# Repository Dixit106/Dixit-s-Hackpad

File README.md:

# Dixit's Hackpad

This is a custom 6-key macropad with a rotary encoder designed for the Hack Club Onboard program.

## Features

* 6 Mechanical Switches (Cherry MX style)
* 1 Rotary Encoder (for volume/scrolling)
* 2 RGB LEDs (SK6812 MINI-E)
* Powered by Seeed XIAO RP2040
* Custom 3D Printed Case (PLA) with snap-fit lid
* Custom PCB Art

## Bill of Materials (BOM)

| Part            | Quantity | Description                               |
| :-------------- | :------- | :---------------------------------------- |
| Microcontroller | 1        | Seeed Studio XIAO RP2040                  |
| Switches        | 6        | Cherry MX Compatible Mechanical Switches  |
| Rotary Encoder  | 1        | EC11 Rotary Encoder                       |
| LEDs            | 2        | SK6812 MINI-E RGB LEDs                    |
| Case            | 1        | Custom 3D Printed PLA Case (Top & Bottom) |
| PCB             | 1        | Custom Designed PCB                       |

## Gallery

### PCB Design

### Schematic

### 3D Case Design

Final:-(i messed up 3d printed case while i was trying to customize it irl)

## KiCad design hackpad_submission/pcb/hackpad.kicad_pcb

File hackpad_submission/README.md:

# Dixit's Hackpad

This is a custom 6-key macropad with a rotary encoder designed for the Hack Club Onboard program.

## Features

* 6 Mechanical Switches (Cherry MX style)
* 1 Rotary Encoder (for volume/scrolling)
* 2 RGB LEDs (SK6812 MINI-E)
* Powered by Seeed XIAO RP2040
* Custom 3D Printed Case (PLA) with snap-fit lid
* Custom PCB Art

## Bill of Materials (BOM)

| Part            | Quantity | Description                               |
| :-------------- | :------- | :---------------------------------------- |
| Microcontroller | 1        | Seeed Studio XIAO RP2040                  |
| Switches        | 6        | Cherry MX Compatible Mechanical Switches  |
| Rotary Encoder  | 1        | EC11 Rotary Encoder                       |
| LEDs            | 2        | SK6812 MINI-E RGB LEDs                    |
| Case            | 1        | Custom 3D Printed PLA Case (Top & Bottom) |
| PCB             | 1        | Custom Designed PCB                       |

## Gallery

### PCB Design

### Schematic

### 3D Case Design

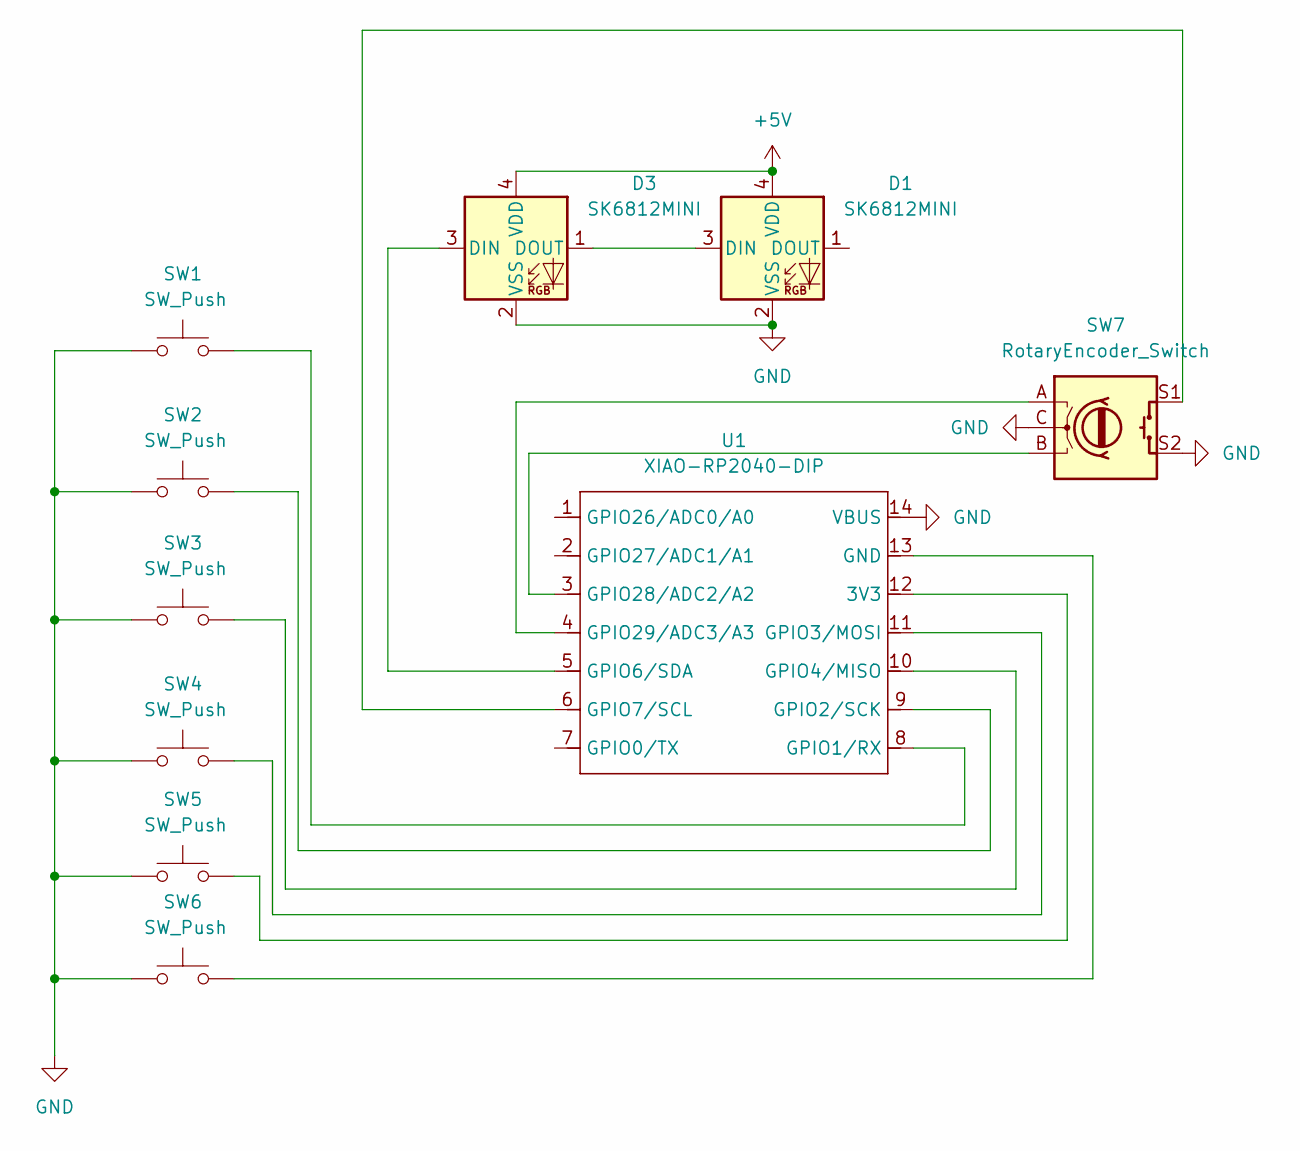
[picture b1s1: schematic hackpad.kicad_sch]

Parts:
D1, D3: SK6812MINI; LED_SK6812MINI_PLCC4_3.5x3.5mm_P1.75mm
SW1, SW2, SW3, SW4, SW5, SW6: SW_Push; SW_Cherry_MX_1.00u_PCB
SW7: RotaryEncoder_Switch; RotaryEncoder_Alps_EC11E-Switch_Vertical_H20mm_CircularMoun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
U1: XIAO-RP2040-DIP; XIAO-RP2040-SMD

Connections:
+5V: D1.4 (VDD), D3.4 (VDD)
GND: D1.2 (VSS), D3.2 (VSS), SW1.1, SW2.1, SW3.1, SW4.1, SW5.1, SW6.1, SW7.C, SW7.S2, U1.14 (VBUS)
unnamed: D1.3 (DIN), D3.1 (DOUT)
unnamed: D3.3 (DIN), U1.5 (GPIO6/SDA)
unnamed: SW5.2, U1.12 (3V3)
unnamed: SW6.2, U1.13 (GND)
unnamed: SW1.2, U1.8 (GPIO1/RX)
unnamed: SW2.2, U1.9 (GPIO2/SCK)
unnamed: SW4.2, U1.11 (GPIO3/MOSI)
unnamed: SW3.2, U1.10 (GPIO4/MISO)
unnamed: SW7.S1, U1.6 (GPIO7/SCL)
unnamed: SW7.B, U1.3 (GPIO28/ADC2/A2)
unnamed: SW7.A, U1.4 (GPIO29/ADC3/A3)

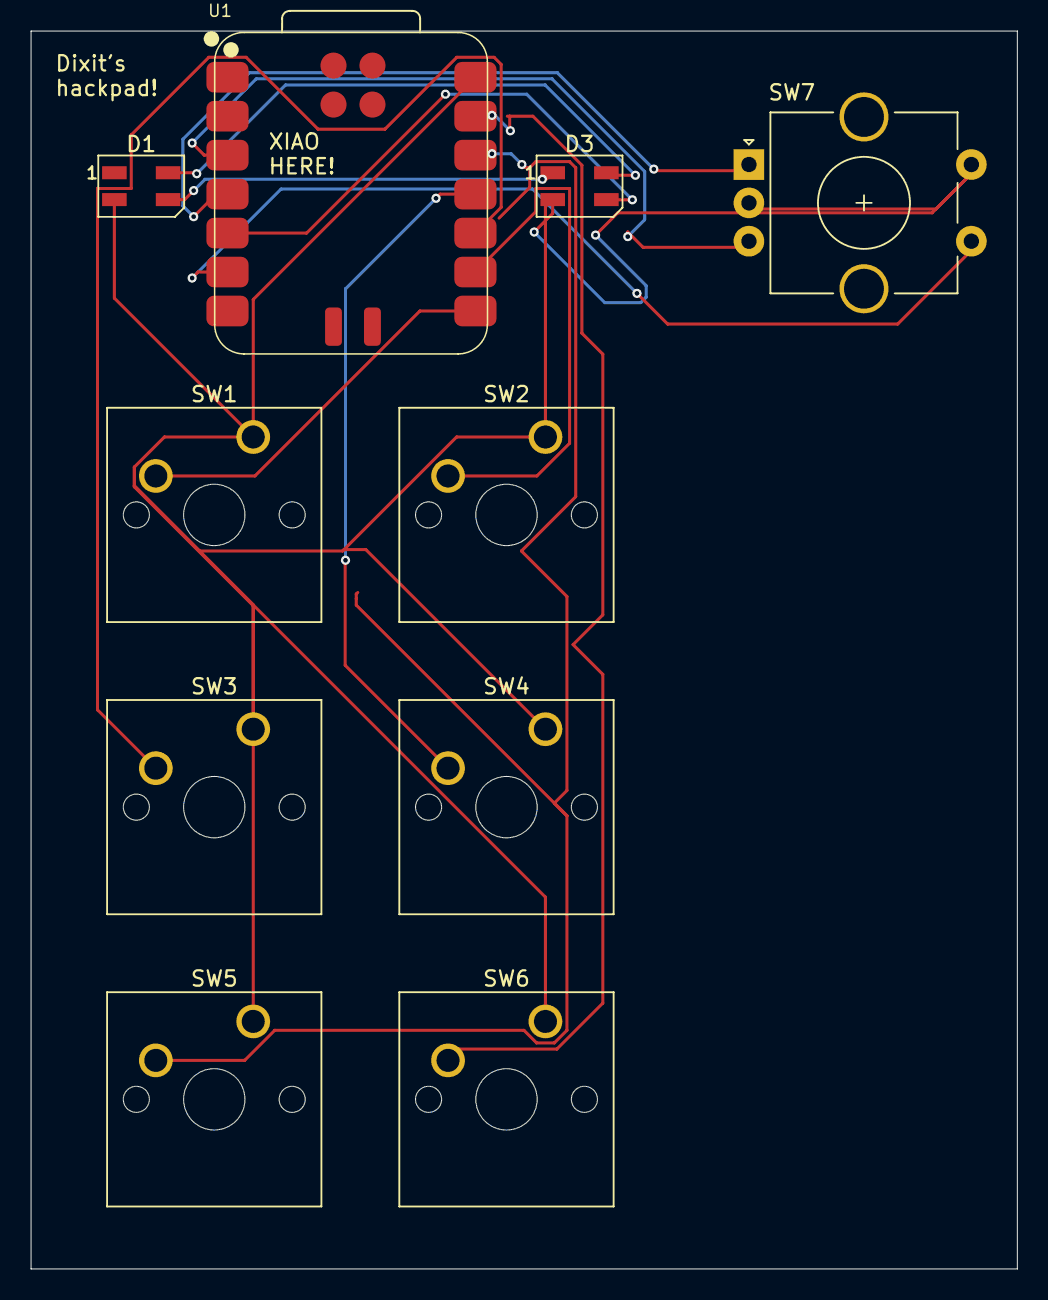
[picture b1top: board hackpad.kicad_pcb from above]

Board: 2 copper layers, 64.3 x 80.7 mm, 10 parts (0 on the bottom side), 13 nets.

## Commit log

2025-12-01 Add files via upload
    "Final Submission"
